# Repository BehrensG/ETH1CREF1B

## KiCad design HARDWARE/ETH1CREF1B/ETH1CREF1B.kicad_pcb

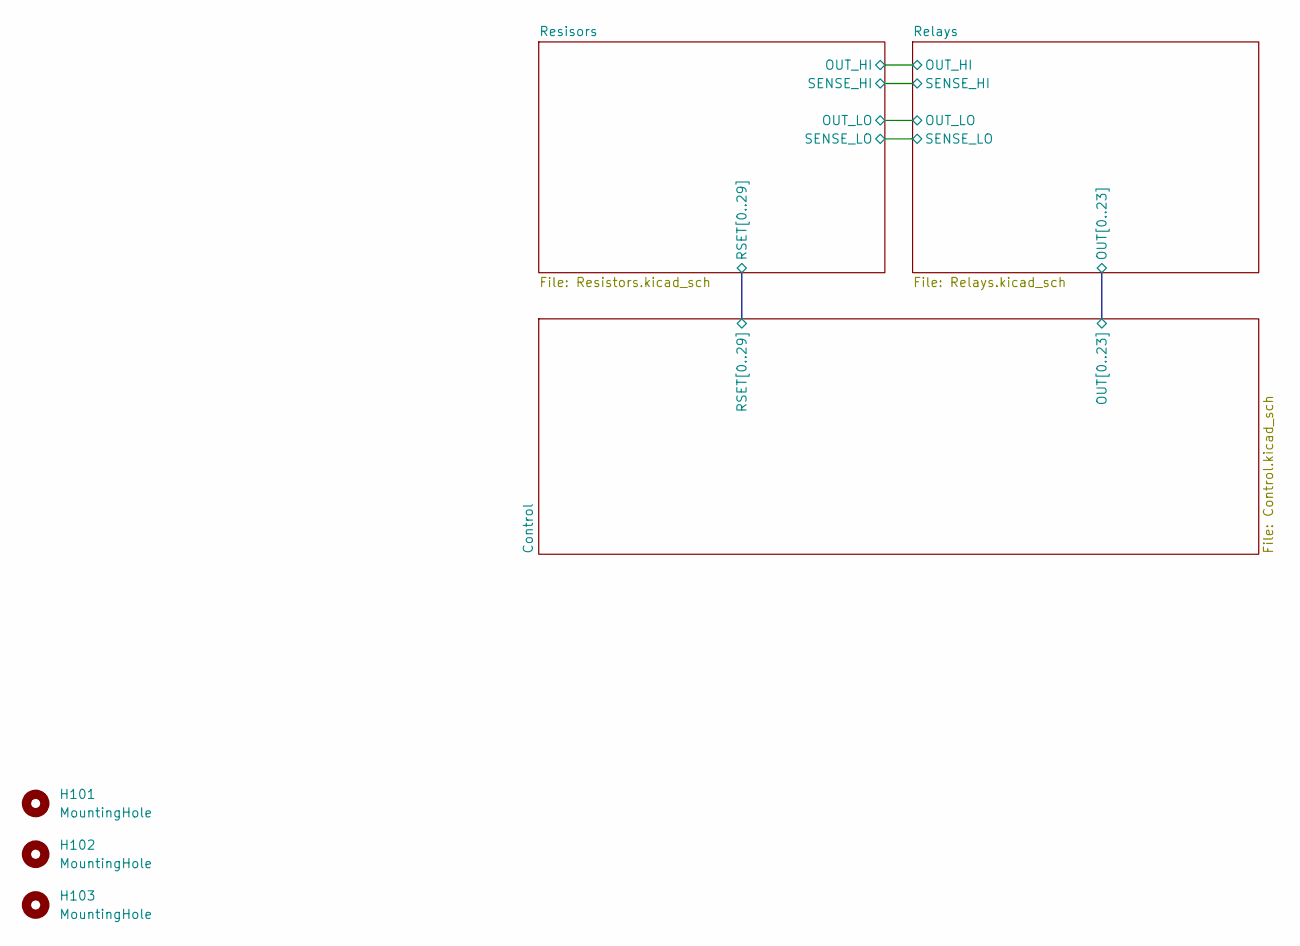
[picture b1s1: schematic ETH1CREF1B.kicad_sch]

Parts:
H101, H102, H103: MountingHole; MountingHole_3.2mm_M3_DIN965_Pad_TopBottom

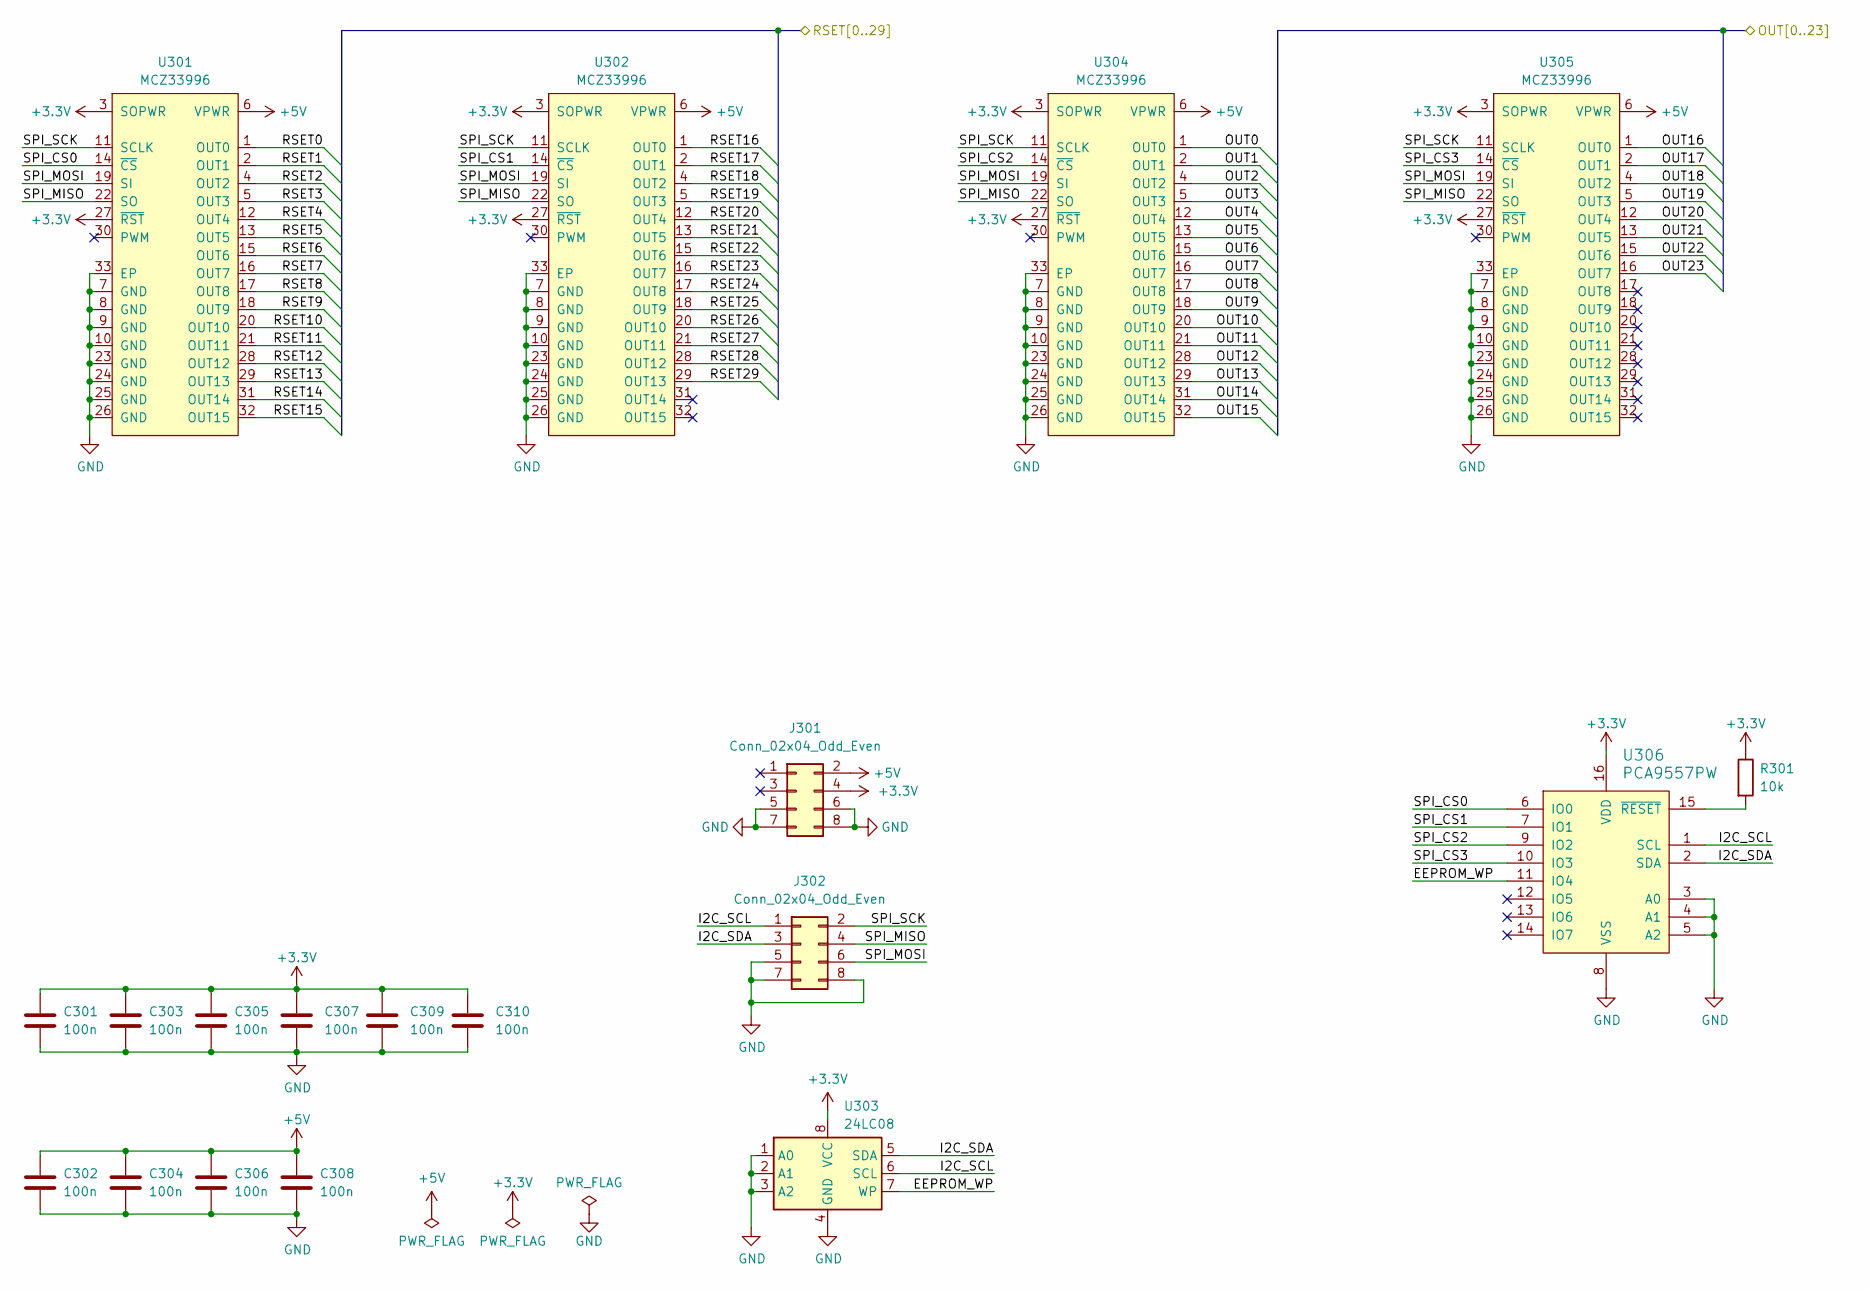
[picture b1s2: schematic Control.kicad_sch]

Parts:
C301, C302, C303, C304, C305, C306, C307, C308, C309, C310: 100n; C_0603_1608Metric_Pad1.08x0.95mm_HandSolder
J301, J302: Conn_02x04_Odd_Even; PinHeader_2x04_P2.54mm_Vertical
R301: 10k; R_0603_1608Metric_Pad0.98x0.95mm_HandSolder
U301, U302, U304, U305: MCZ33996; HSOP-32-1EP_7.5x11.0mm_P0.65mm_ThermalVias
U303: 24LC08; MSOP-8_3x3mm_P0.65mm
U306: PCA9557PW; TSSOP-16_4.4x5mm_P0.65mm

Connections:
+3.3V: C301.1, C303.1, C305.1, C307.1, C309.1, C310.1, J301.4, R301.1, U301.3 (SOPWR), U301.27 (~RST), U302.3 (SOPWR), U302.27 (~RST), U303.8 (VCC), U304.3 (SOPWR), U304.27 (~RST), U305.3 (SOPWR), U305.27 (~RST), U306.16 (VDD)
+5V: C302.1, C304.1, C306.1, C308.1, J301.2, U301.6 (VPWR), U302.6 (VPWR), U304.6 (VPWR), U305.6 (VPWR); also elsewhere on the board
/Control/EEPROM_WP: U303.7 (WP), U306.11 (IO4)
/Control/I2C_SCL: J302.1, U303.6 (SCL), U306.1 (SCL)
/Control/I2C_SDA: J302.3, U303.5 (SDA), U306.2 (SDA)
/Control/OUT0: U304.1 (OUT0); also elsewhere on the board
/Control/OUT1: U304.2 (OUT1); also elsewhere on the board
/Control/OUT2: U304.4 (OUT2); also elsewhere on the board
/Control/OUT3: U304.5 (OUT3); also elsewhere on the board
/Control/OUT4: U304.12 (OUT4); also elsewhere on the board
/Control/OUT5: U304.13 (OUT5); also elsewhere on the board
/Control/OUT6: U304.15 (OUT6); also elsewhere on the board
/Control/OUT7: U304.16 (OUT7); also elsewhere on the board
/Control/OUT8: U304.17 (OUT8); also elsewhere on the board
/Control/OUT9: U304.18 (OUT9); also elsewhere on the board
/Control/OUT10: U304.20 (OUT10); also elsewhere on the board
/Control/OUT11: U304.21 (OUT11); also elsewhere on the board
/Control/OUT12: U304.28 (OUT12); also elsewhere on the board
/Control/OUT13: U304.29 (OUT13); also elsewhere on the board
/Control/OUT14: U304.31 (OUT14); also elsewhere on the board
/Control/OUT15: U304.32 (OUT15); also elsewhere on the board
/Control/OUT16: U305.1 (OUT0); also elsewhere on the board
/Control/OUT17: U305.2 (OUT1); also elsewhere on the board
/Control/OUT18: U305.4 (OUT2); also elsewhere on the board
/Control/OUT19: U305.5 (OUT3); also elsewhere on the board
/Control/OUT20: U305.12 (OUT4); also elsewhere on the board
/Control/OUT21: U305.13 (OUT5); also elsewhere on the board
/Control/OUT22: U305.15 (OUT6); also elsewhere on the board
/Control/OUT23: U305.16 (OUT7); also elsewhere on the board
/Control/RSET0: U301.1 (OUT0); also elsewhere on the board
/Control/RSET1: U301.2 (OUT1); also elsewhere on the board
/Control/RSET2: U301.4 (OUT2); also elsewhere on the board
/Control/RSET3: U301.5 (OUT3); also elsewhere on the board
/Control/RSET4: U301.12 (OUT4); also elsewhere on the board
/Control/RSET5: U301.13 (OUT5); also elsewhere on the board
/Control/RSET6: U301.15 (OUT6); also elsewhere on the board
/Control/RSET7: U301.16 (OUT7); also elsewhere on the board
/Control/RSET8: U301.17 (OUT8); also elsewhere on the board
/Control/RSET9: U301.18 (OUT9); also elsewhere on the board
/Control/RSET10: U301.20 (OUT10)
/Control/RSET11: U301.21 (OUT11); also elsewhere on the board
/Control/RSET12: U301.28 (OUT12); also elsewhere on the board
/Control/RSET13: U301.29 (OUT13); also elsewhere on the board
/Control/RSET14: U301.31 (OUT14); also elsewhere on the board
/Control/RSET15: U301.32 (OUT15); also elsewhere on the board
/Control/RSET16: U302.1 (OUT0); also elsewhere on the board
/Control/RSET17: U302.2 (OUT1); also elsewhere on the board
/Control/RSET18: U302.4 (OUT2); also elsewhere on the board
/Control/RSET19: U302.5 (OUT3); also elsewhere on the board
/Control/RSET20: U302.12 (OUT4); also elsewhere on the board
/Control/RSET21: U302.13 (OUT5); also elsewhere on the board
/Control/RSET22: U302.15 (OUT6); also elsewhere on the board
/Control/RSET23: U302.16 (OUT7); also elsewhere on the board
/Control/RSET24: U302.17 (OUT8); also elsewhere on the board
/Control/RSET25: U302.18 (OUT9); also elsewhere on the board
/Control/RSET26: U302.20 (OUT10); also elsewhere on the board
/Control/RSET27: U302.21 (OUT11); also elsewhere on the board
/Control/RSET28: U302.28 (OUT12); also elsewhere on the board
/Control/RSET29: U302.29 (OUT13); also elsewhere on the board
/Control/SPI_CS0: U301.14 (~CS), U306.6 (IO0)
/Control/SPI_CS1: U302.14 (~CS), U306.7 (IO1)
/Control/SPI_CS2: U304.14 (~CS), U306.9 (IO2)
/Control/SPI_CS3: U305.14 (~CS), U306.10 (IO3)
/Control/SPI_MISO: J302.4, U301.22 (SO), U302.22 (SO), U304.22 (SO), U305.22 (SO)
/Control/SPI_MOSI: J302.6, U301.19 (SI), U302.19 (SI), U304.19 (SI), U305.19 (SI)
/Control/SPI_SCK: J302.2, U301.11 (SCLK), U302.11 (SCLK), U304.11 (SCLK), U305.11 (SCLK)
GND: C301.2, C302.2, C303.2, C304.2, C305.2, C306.2, C307.2, C308.2, C309.2, C310.2, J301.5, J301.6, J301.7, J301.8, J302.5, J302.7, J302.8, U301.7 (GND), U301.8 (GND), U301.9 (GND), U301.10 (GND), U301.23 (GND), U301.24 (GND), U301.25 (GND), U301.26 (GND), U301.33 (EP), U302.7 (GND), U302.8 (GND), U302.9 (GND), U302.10 (GND), U302.23 (GND), U302.24 (GND), U302.25 (GND), U302.26 (GND), U302.33 (EP), U303.1 (A0), U303.2 (A1), U303.3 (A2), U303.4 (GND), U304.7 (GND), U304.8 (GND), U304.9 (GND), U304.10 (GND), U304.23 (GND), U304.24 (GND), U304.25 (GND), U304.26 (GND), U304.33 (EP), U305.7 (GND), U305.8 (GND), U305.9 (GND), U305.10 (GND), U305.23 (GND), U305.24 (GND), U305.25 (GND), U305.26 (GND), U305.33 (EP), U306.3 (A0), U306.4 (A1), U306.5 (A2), U306.8 (VSS)
unnamed: R301.2, U306.15 (~RESET)

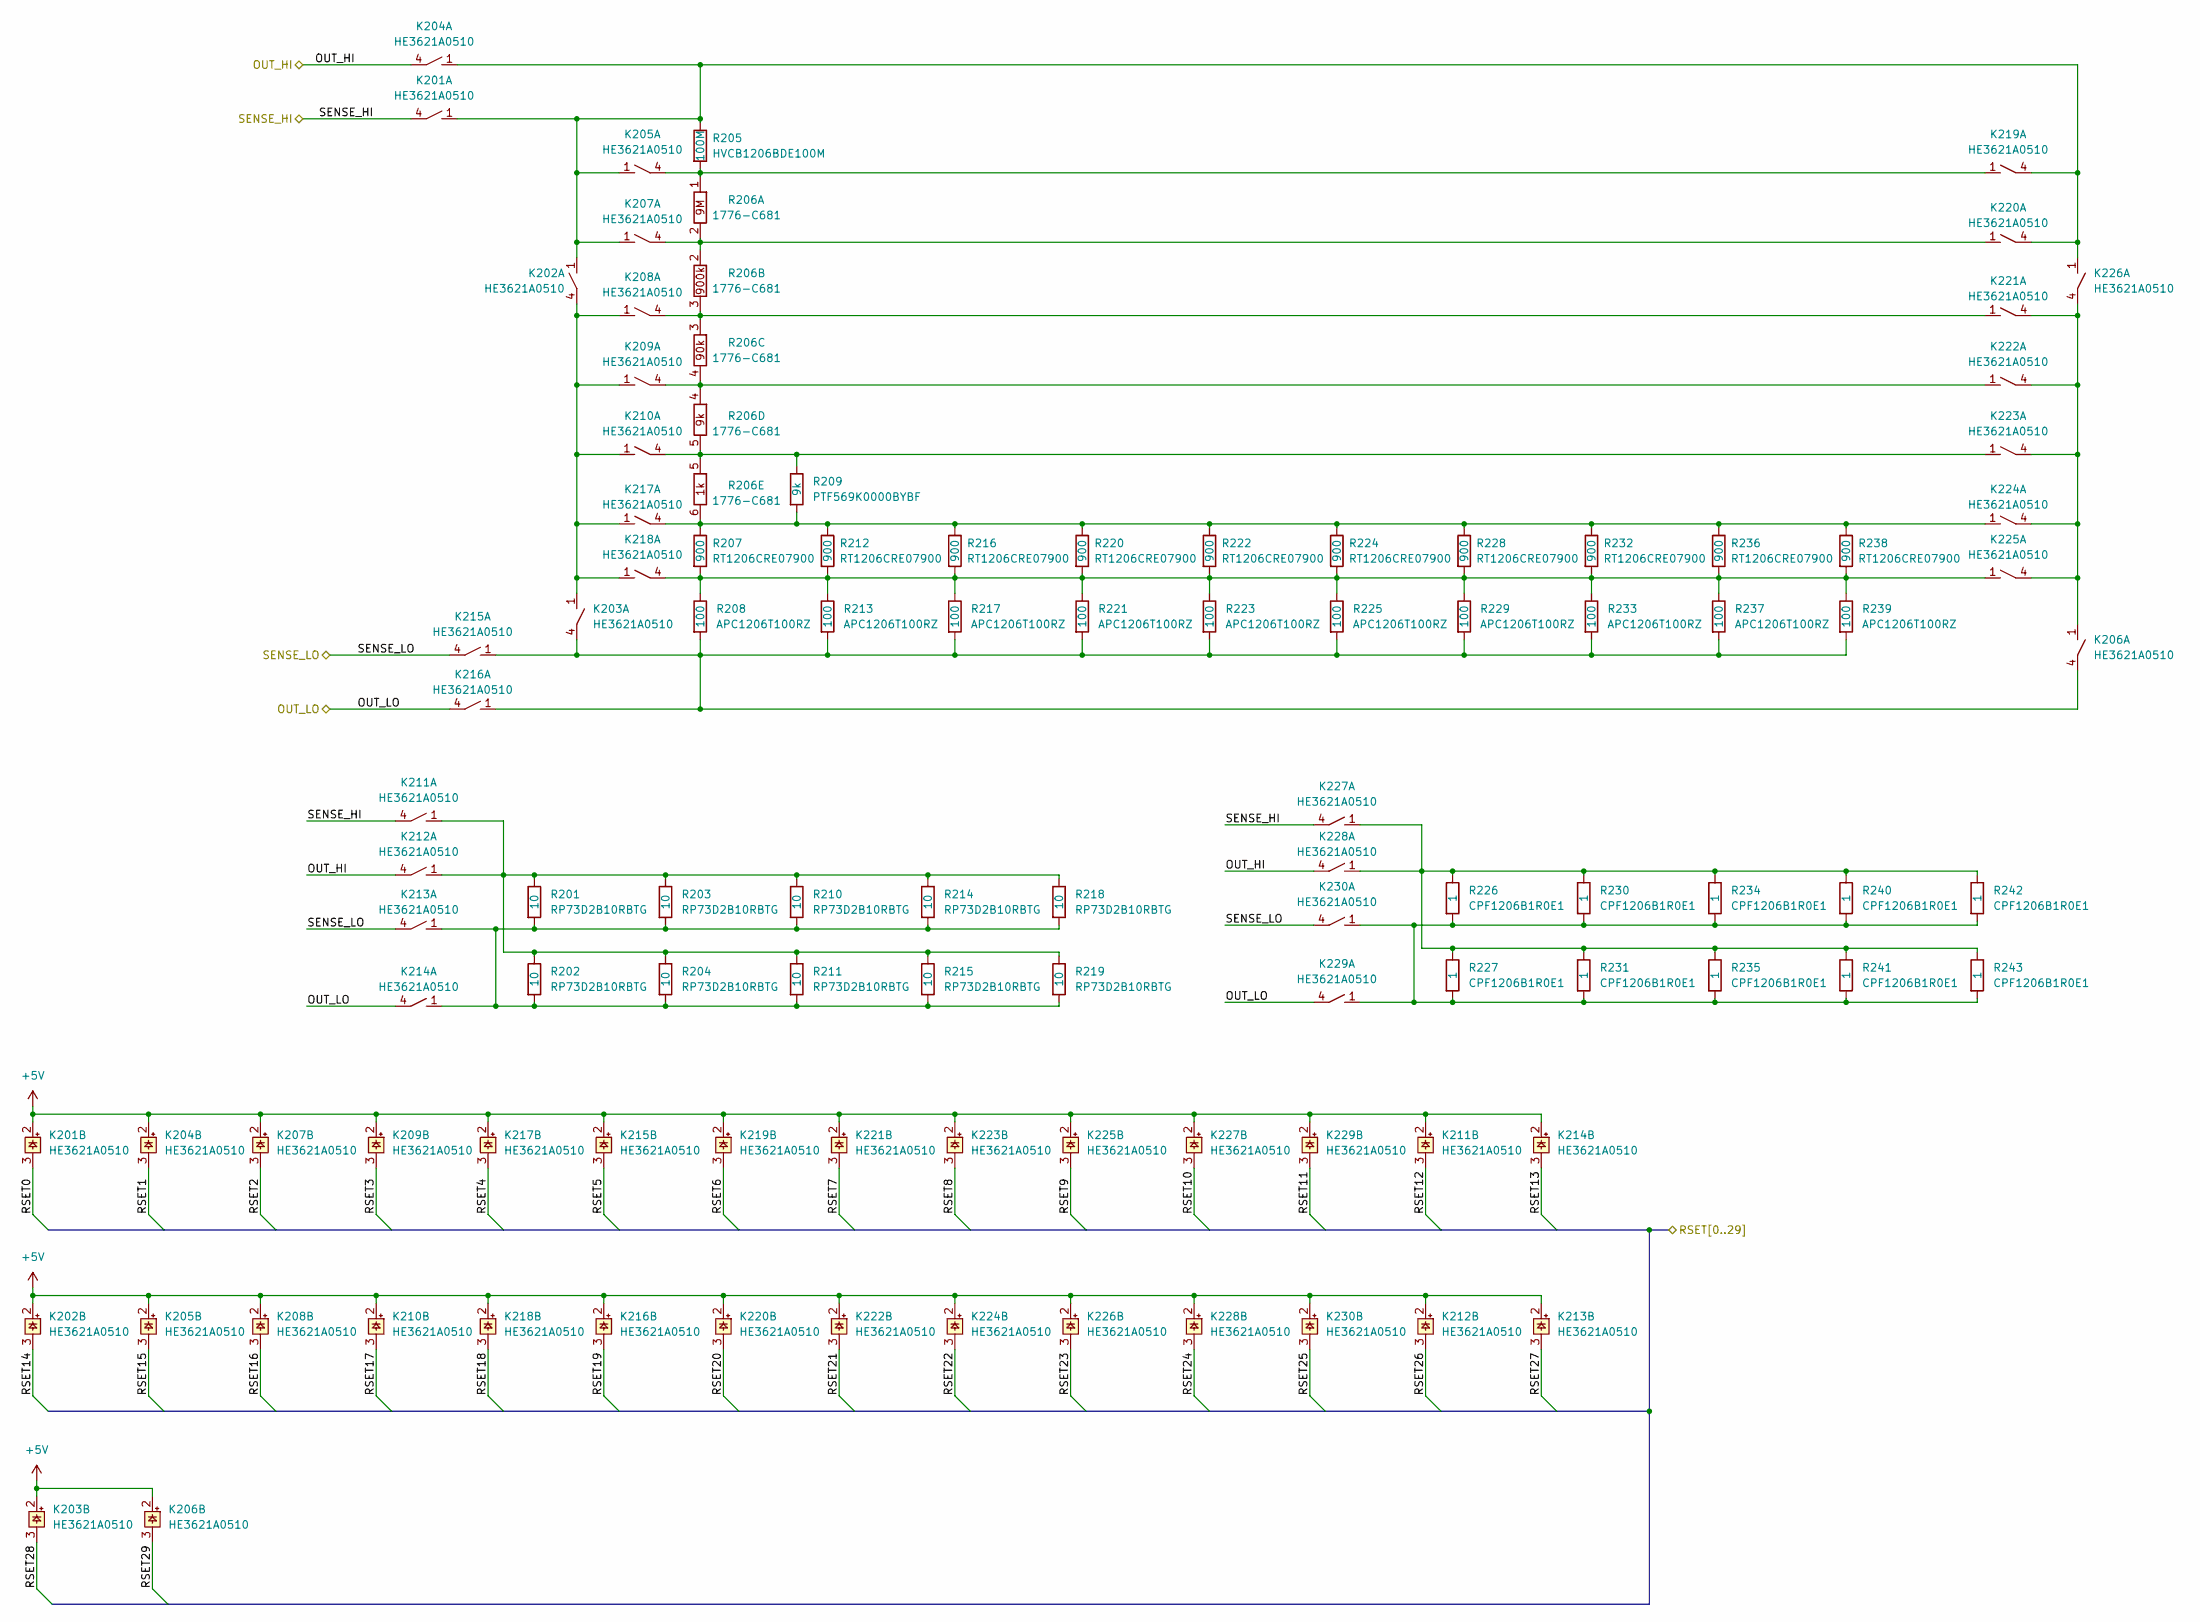
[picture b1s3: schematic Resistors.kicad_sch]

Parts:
K201, K202, K203, K204, K205, K206, K207, K208, K209, K210, K211, K212, K213, K214, K215, K216, K217, K218, K219, K220, K221, K222, K223, K224, K225, K226, K227, K228, K229, K230: HE3621A0510; HE360_x-5050462-8
R201, R202, R203, R204, R210, R211, R214, R215, R218, R219: RP73D2B10RBTG; R_1206_3216Metric_Pad1.30x1.75mm_HandSolder
R205: HVCB1206BDE100M; R_1206_3216Metric_Pad1.30x1.75mm_HandSolder
R206: 1776-C681
R207, R212, R216, R220, R222, R224, R228, R232, R236, R238: RT1206CRE07900; R_1206_3216Metric_Pad1.30x1.75mm_HandSolder
R208, R213, R217, R221, R223, R225, R229, R233, R237, R239: APC1206T100RZ; R_1206_3216Metric_Pad1.30x1.75mm_HandSolder
R209: PTF569K0000BYBF; R_Axial_DIN0207_L6.3mm_D2.5mm_P15.24mm_Horizontal
R226, R227, R230, R231, R234, R235, R240, R241, R242, R243: CPF1206B1R0E1; R_1206_3216Metric_Pad1.30x1.75mm_HandSolder

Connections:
+5V: K201.2, K202.2, K203.2, K204.2, K205.2, K206.2, K207.2, K208.2, K209.2, K210.2, K211.2, K212.2, K213.2, K214.2, K215.2, K216.2, K217.2, K218.2, K219.2, K220.2, K221.2, K222.2, K223.2, K224.2, K225.2, K226.2, K227.2, K228.2, K229.2, K230.2; also elsewhere on the board
/Control/RSET0: K201.3; also elsewhere on the board
/Control/RSET1: K204.3; also elsewhere on the board
/Control/RSET2: K207.3; also elsewhere on the board
/Control/RSET3: K209.3; also elsewhere on the board
/Control/RSET4: K217.3; also elsewhere on the board
/Control/RSET5: K215.3; also elsewhere on the board
/Control/RSET6: K219.3; also elsewhere on the board
/Control/RSET7: K221.3; also elsewhere on the board
/Control/RSET8: K223.3; also elsewhere on the board
/Control/RSET9: K225.3; also elsewhere on the board
/Control/RSET11: K229.3; also elsewhere on the board
/Control/RSET12: K211.3; also elsewhere on the board
/Control/RSET13: K214.3; also elsewhere on the board
/Control/RSET14: K202.3; also elsewhere on the board
/Control/RSET15: K205.3; also elsewhere on the board
/Control/RSET16: K208.3; also elsewhere on the board
/Control/RSET17: K210.3; also elsewhere on the board
/Control/RSET18: K218.3; also elsewhere on the board
/Control/RSET19: K216.3; also elsewhere on the board
/Control/RSET20: K220.3; also elsewhere on the board
/Control/RSET21: K222.3; also elsewhere on the board
/Control/RSET22: K224.3; also elsewhere on the board
/Control/RSET23: K226.3; also elsewhere on the board
/Control/RSET24: K228.3; also elsewhere on the board
/Control/RSET25: K230.3; also elsewhere on the board
/Control/RSET26: K212.3; also elsewhere on the board
/Control/RSET27: K213.3; also elsewhere on the board
/Control/RSET28: K203.3; also elsewhere on the board
/Control/RSET29: K206.3; also elsewhere on the board
/Resisors/OUT_HI: K204.4, K212.4, K228.4; also elsewhere on the board
/Resisors/OUT_LO: K214.4, K216.4, K229.4; also elsewhere on the board
/Resisors/SENSE_HI: K201.4, K211.4, K227.4; also elsewhere on the board
/Resisors/SENSE_LO: K213.4, K215.4, K230.4; also elsewhere on the board
unnamed: K201.1, K202.1, K204.1, K205.1, K207.1, K219.4, K220.4, K226.1, R205.1
unnamed: K202.4, K203.1, K208.1, K209.1, K210.1, K217.1, K218.1
unnamed: K203.4, K206.4, K215.1, K216.1, R208.2, R213.2, R217.2, R221.2, R223.2, R225.2, R229.2, R233.2, R237.2, R239.2
unnamed: K205.4, K219.1, R205.2, R206.1
unnamed: K206.1, K221.4, K222.4, K223.4, K224.4, K225.4, K226.4
unnamed: K207.4, K220.1, R206.2
unnamed: K208.4, K221.1, R206.3
unnamed: K209.4, K222.1, R206.4
unnamed: K210.4, K223.1, R206.5, R209.1
unnamed: K211.1, K212.1, R201.1, R202.1, R203.1, R204.1, R210.1, R211.1, R214.1, R215.1, R218.1, R219.1
unnamed: K213.1, K214.1, R201.2, R202.2, R203.2, R204.2, R210.2, R211.2, R214.2, R215.2, R218.2, R219.2
unnamed: K217.4, K224.1, R206.6, R207.1, R209.2, R212.1, R216.1, R220.1, R222.1, R224.1, R228.1, R232.1, R236.1, R238.1
unnamed: K218.4, K225.1, R207.2, R208.1, R212.2, R213.1, R216.2, R217.1, R220.2, R221.1, R222.2, R223.1, R224.2, R225.1, R228.2, R229.1, R232.2, R233.1, R236.2, R237.1, R238.2, R239.1
unnamed: K227.1, K228.1, R226.1, R227.1, R230.1, R231.1, R234.1, R235.1, R240.1, R241.1, R242.1, R243.1
unnamed: K229.1, K230.1, R226.2, R227.2, R230.2, R231.2, R234.2, R235.2, R240.2, R241.2, R242.2, R243.2

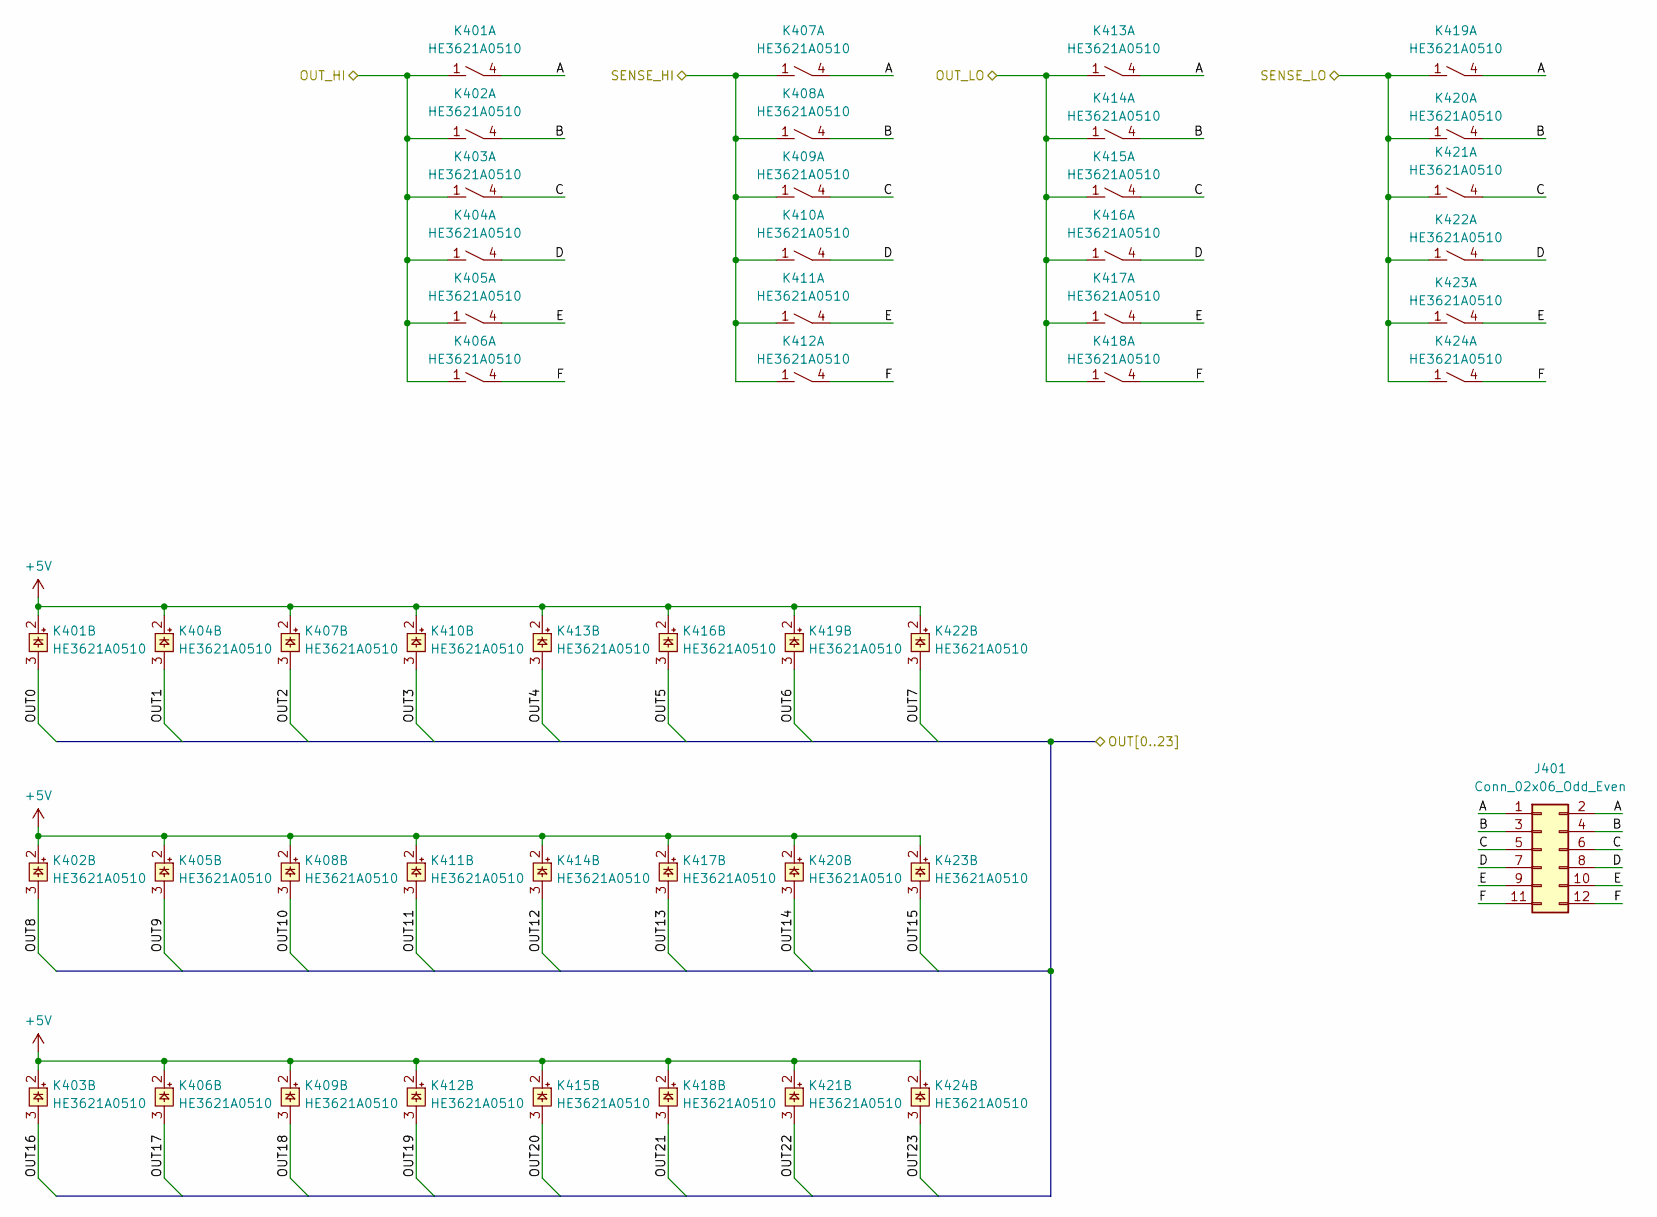
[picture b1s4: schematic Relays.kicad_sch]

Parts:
J401: Conn_02x06_Odd_Even; PinHeader_2x06_P2.54mm_Vertical
K401, K402, K403, K404, K405, K406, K407, K408, K409, K410, K411, K412, K413, K414, K415, K416, K417, K418, K419, K420, K421, K422, K423, K424: HE3621A0510; HE360_x-5050462-8

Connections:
+5V: K401.2, K402.2, K403.2, K404.2, K405.2, K406.2, K407.2, K408.2, K409.2, K410.2, K411.2, K412.2, K413.2, K414.2, K415.2, K416.2, K417.2, K418.2, K419.2, K420.2, K421.2, K422.2, K423.2, K424.2; also elsewhere on the board
/Control/OUT0: K401.3; also elsewhere on the board
/Control/OUT1: K404.3; also elsewhere on the board
/Control/OUT2: K407.3; also elsewhere on the board
/Control/OUT3: K410.3; also elsewhere on the board
/Control/OUT4: K413.3; also elsewhere on the board
/Control/OUT5: K416.3; also elsewhere on the board
/Control/OUT6: K419.3; also elsewhere on the board
/Control/OUT7: K422.3; also elsewhere on the board
/Control/OUT8: K402.3; also elsewhere on the board
/Control/OUT9: K405.3; also elsewhere on the board
/Control/OUT10: K408.3; also elsewhere on the board
/Control/OUT11: K411.3; also elsewhere on the board
/Control/OUT12: K414.3; also elsewhere on the board
/Control/OUT13: K417.3; also elsewhere on the board
/Control/OUT14: K420.3; also elsewhere on the board
/Control/OUT15: K423.3; also elsewhere on the board
/Control/OUT16: K403.3; also elsewhere on the board
/Control/OUT17: K406.3; also elsewhere on the board
/Control/OUT18: K409.3; also elsewhere on the board
/Control/OUT19: K412.3; also elsewhere on the board
/Control/OUT20: K415.3; also elsewhere on the board
/Control/OUT21: K418.3; also elsewhere on the board
/Control/OUT22: K421.3; also elsewhere on the board
/Control/OUT23: K424.3; also elsewhere on the board
/Relays/A: J401.1, J401.2, K401.4, K407.4, K413.4, K419.4
/Relays/B: J401.3, J401.4, K402.4, K408.4, K414.4, K420.4
/Relays/C: J401.5, J401.6, K403.4, K409.4, K415.4, K421.4
/Relays/D: J401.7, J401.8, K404.4, K410.4, K416.4, K422.4
/Relays/E: J401.9, J401.10, K405.4, K411.4, K417.4, K423.4
/Relays/F: J401.11, J401.12, K406.4, K412.4, K418.4, K424.4
/Resisors/OUT_HI: K401.1, K402.1, K403.1, K404.1, K405.1, K406.1; also elsewhere on the board
/Resisors/OUT_LO: K413.1, K414.1, K415.1, K416.1, K417.1, K418.1; also elsewhere on the board
/Resisors/SENSE_HI: K407.1, K408.1, K409.1, K410.1, K411.1, K412.1; also elsewhere on the board
/Resisors/SENSE_LO: K419.1, K420.1, K421.1, K422.1, K423.1, K424.1; also elsewhere on the board

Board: 4 copper layers, 120 parts (20 on the bottom side), 92 nets, no tracks yet.

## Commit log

2023-07-08 Hardware
